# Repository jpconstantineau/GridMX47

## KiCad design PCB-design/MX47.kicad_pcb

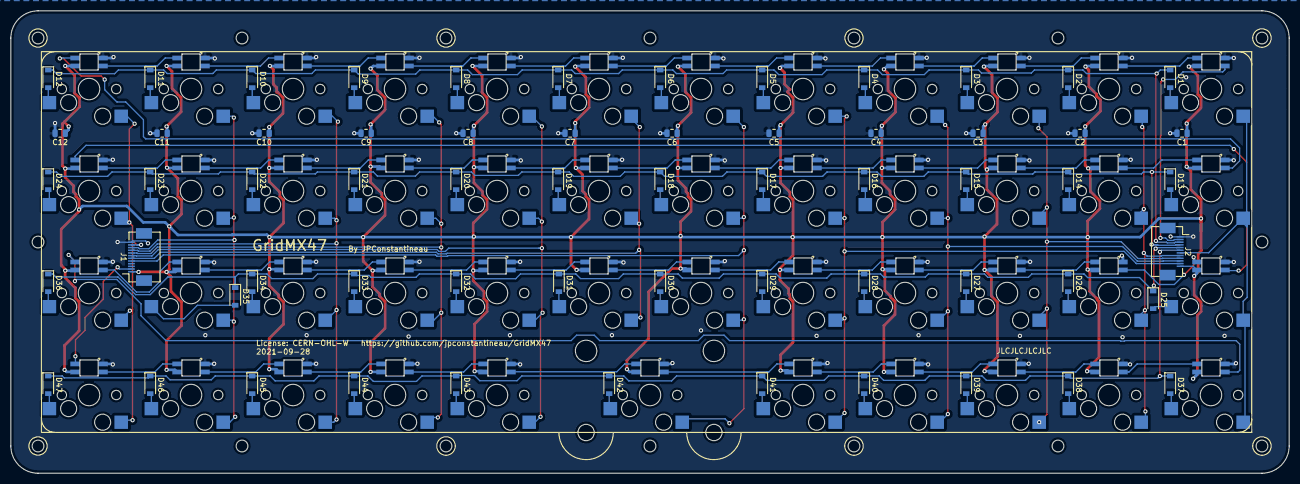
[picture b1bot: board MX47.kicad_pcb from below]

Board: 2 copper layers, 238.8 x 86.4 mm, 124 parts (61 on the bottom side), 113 nets.

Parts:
C1, C2, C3, C4, C5, C6, C7, C8, C9, C10, C11, C12: 1uF; C_0805_2012Metric
D1, D2, D3, D4, D5, D6, D7, D8, D9, D10, D11, D12, D13, D14, D15, D16, D17, D18, D19, D20, D21, D22, D23, D24, D25, D26, D27, D28, D29, D30, D31, D32, D33, D34, D35, D36, D37, D38, D39, D40, D41, D42, D43, D44, D45, D46, D47: D; D_SOD-123
H1, H2, H3, H4, H5, H6, H7, H8, H9, H10, H11, H12, H13, H14, H15, H16: MountingHole; MountingHole_2.2mm_M2
J1, J2: Conn_01x12; JUSHUO-AFC07-S12FCC-00_C11051_1x12-1MP_P0.50mm_Horizontal
U1, U2, U3, U4, U5, U6, U7, U8, U9, U10, U11, U12, U13, U14, U15, U16, U17, U18, U19, U20, U21, U22, U23, U24, U25, U26, U27, U28, U29, U30, U31, U32, U33, U34, U35, U36, U37, U38, U39, U40, U41, U43, U44, U45, U46, U47: CherryMX_LTST-A683CEGBW; CherryMX_1.00u_PCB_KailhSocket_LTST-A683CEGBW-Rotated
U42: CherryMX_LTST-A683CEGBW; CherryMX_2.00u_PCB_KailhSocket_StabWireBottom_LTST-A683CEGB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

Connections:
COL1: J2.7, U1.2, U13.2, U25.2, U37.2
COL2: J2.8, U2.2, U14.2, U26.2, U38.2
COL3: J2.9, U3.2, U15.2, U27.2, U39.2
COL4: J2.10, U4.2, U16.2, U28.2, U40.2
COL5: J2.11, U5.2, U17.2, U29.2, U41.2
COL6: J1.5, U6.2, U18.2, U30.2, U42.2
COL7: J1.6, U7.2, U19.2, U31.2
COL8: J1.7, U8.2, U20.2, U32.2, U43.2
COL9: J1.8, U9.2, U21.2, U33.2, U44.2
COL10: J1.9, U10.2, U22.2, U34.2, U45.2
COL11: J1.10, U11.2, U23.2, U35.2, U46.2
COL12: J1.11, U12.2, U24.2, U36.2, U47.2
GND: C1.2, C2.2, C3.2, C4.2, C5.2, C6.2, C7.2, C8.2, C9.2, C10.2, C11.2, C12.2, J1.12, J2.1, U1.3, U2.3, U3.3, U4.3, U5.3, U6.3, U7.3, U8.3, U9.3, U10.3, U11.3, U12.3, U13.3, U14.3, U15.3, U16.3, U17.3, U18.3, U19.3, U20.3, U21.3, U22.3, U23.3, U24.3, U25.3, U26.3, U27.3, U28.3, U29.3, U30.3, U31.3, U32.3, U33.3, U34.3, U35.3, U36.3, U37.3, U38.3, U39.3, U40.3, U41.3, U42.3, U43.3, U44.3, U45.3, U46.3, U47.3
unnamed: D1.2, U1.1
unnamed: D2.2, U2.1
unnamed: D3.2, U3.1
unnamed: D4.2, U4.1
unnamed: D5.2, U5.1
unnamed: D6.2, U6.1
unnamed: D7.2, U7.1
unnamed: D8.2, U8.1
unnamed: D9.2, U9.1
unnamed: D10.2, U10.1
unnamed: D11.2, U11.1
unnamed: D12.2, U12.1
unnamed: D13.2, U13.1
unnamed: D14.2, U14.1
unnamed: D15.2, U15.1
unnamed: D16.2, U16.1
unnamed: D17.2, U17.1
unnamed: D18.2, U18.1
unnamed: D19.2, U19.1
unnamed: D20.2, U20.1
unnamed: D21.2, U21.1
unnamed: D22.2, U22.1
unnamed: D23.2, U23.1
unnamed: D24.2, U24.1
unnamed: D25.2, U25.1
unnamed: D26.2, U26.1
unnamed: D27.2, U27.1
unnamed: D28.2, U28.1
unnamed: D29.2, U29.1
unnamed: D30.2, U30.1
unnamed: D31.2, U31.1
unnamed: D32.2, U32.1
unnamed: D33.2, U33.1
unnamed: D34.2, U34.1
unnamed: D35.2, U35.1
unnamed: D36.2, U36.1
unnamed: D37.2, U37.1
unnamed: D38.2, U38.1
unnamed: D39.2, U39.1
unnamed: D40.2, U40.1
unnamed: D41.2, U41.1
unnamed: D42.2, U42.1
unnamed: D43.2, U43.1
unnamed: D44.2, U44.1
unnamed: D45.2, U45.1
unnamed: D46.2, U46.1
unnamed: D47.2, U47.1
unnamed: U1.5, U2.4
unnamed: U2.5, U3.4
unnamed: U3.5, U4.4
unnamed: U4.5, U5.4
unnamed: U5.5, U6.4
unnamed: U6.5, U7.4
unnamed: U7.5, U8.4
unnamed: U8.5, U9.4
unnamed: U9.5, U10.4
unnamed: U10.5, U11.4
unnamed: U11.5, U12.4
unnamed: U12.5, U13.4
unnamed: U13.5, U14.4
unnamed: U14.5, U15.4
unnamed: U15.5, U16.4
unnamed: U16.5, U17.4
unnamed: U17.5, U18.4
unnamed: U18.5, U19.4
unnamed: U19.5, U20.4
unnamed: U20.5, U21.4
unnamed: U21.5, U22.4
unnamed: U22.5, U23.4
unnamed: U23.5, U24.4
unnamed: U24.5, U25.4
unnamed: U25.5, U26.4
unnamed: U26.5, U27.4
unnamed: U27.5, U28.4
unnamed: U28.5, U29.4
unnamed: U29.5, U30.4
unnamed: U30.5, U31.4
unnamed: U31.5, U32.4
unnamed: U32.5, U33.4
unnamed: U33.5, U34.4
unnamed: U34.5, U35.4
unnamed: U35.5, U36.4
unnamed: U36.5, U37.4
unnamed: U37.5, U38.4
unnamed: U38.5, U39.4
unnamed: U39.5, U40.4
unnamed: U40.5, U41.4
unnamed: U41.5, U42.4
unnamed: U42.5, U43.4
unnamed: U43.5, U44.4
unnamed: U44.5, U45.4
unnamed: U45.5, U46.4
unnamed: U46.5, U47.4
RGBData: J2.2, U1.4
RGBOut: J1.2, U47.5
ROW1: D1.1, D2.1, D3.1, D4.1, D5.1, D6.1, D7.1, D8.1, D9.1, D10.1, D11.1, D12.1, J2.3
ROW2: D13.1, D14.1, D15.1, D16.1, D17.1, D18.1, D19.1, D20.1, D21.1, D22.1, D23.1, D24.1, J2.4
ROW3: D25.1, D26.1, D27.1, D28.1, D29.1, D30.1, D31.1, D32.1, D33.1, D34.1, D35.1, D36.1, J2.5
ROW4: D37.1, D38.1, D39.1, D40.1, D41.1, D42.1, D43.1, D44.1, D45.1, D46.1, D47.1, J2.6
VCC: C1.1, C2.1, C3.1, C4.1, C5.1, C6.1, C7.1, C8.1, C9.1, C10.1, C11.1, C12.1, J1.1, J2.12, U1.6, U2.6, U3.6, U4.6, U5.6, U6.6, U7.6, U8.6, U9.6, U10.6, U11.6, U12.6, U13.6, U14.6, U15.6, U16.6, U17.6, U18.6, U19.6, U20.6, U21.6, U22.6, U23.6, U24.6, U25.6, U26.6, U27.6, U28.6, U29.6, U30.6, U31.6, U32.6, U33.6, U34.6, U35.6, U36.6, U37.6, U38.6, U39.6, U40.6, U41.6, U42.6, U43.6, U44.6, U45.6, U46.6, U47.6

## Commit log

2021-09-20 adding initial PCB
2021-09-28 fix spacebar footprint
2021-10-04 minor updates

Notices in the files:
PCB-design/MX47.kicad_pcb:
License: CERN-OHL-W https://github.com/jpconstantineau/GridMX47
